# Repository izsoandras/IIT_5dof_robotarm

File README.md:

Foun an old 5 degree of freedom robotarm (Kalms&Mürb teach-robot) on my department. Decided to give it a new life. here is my progression.

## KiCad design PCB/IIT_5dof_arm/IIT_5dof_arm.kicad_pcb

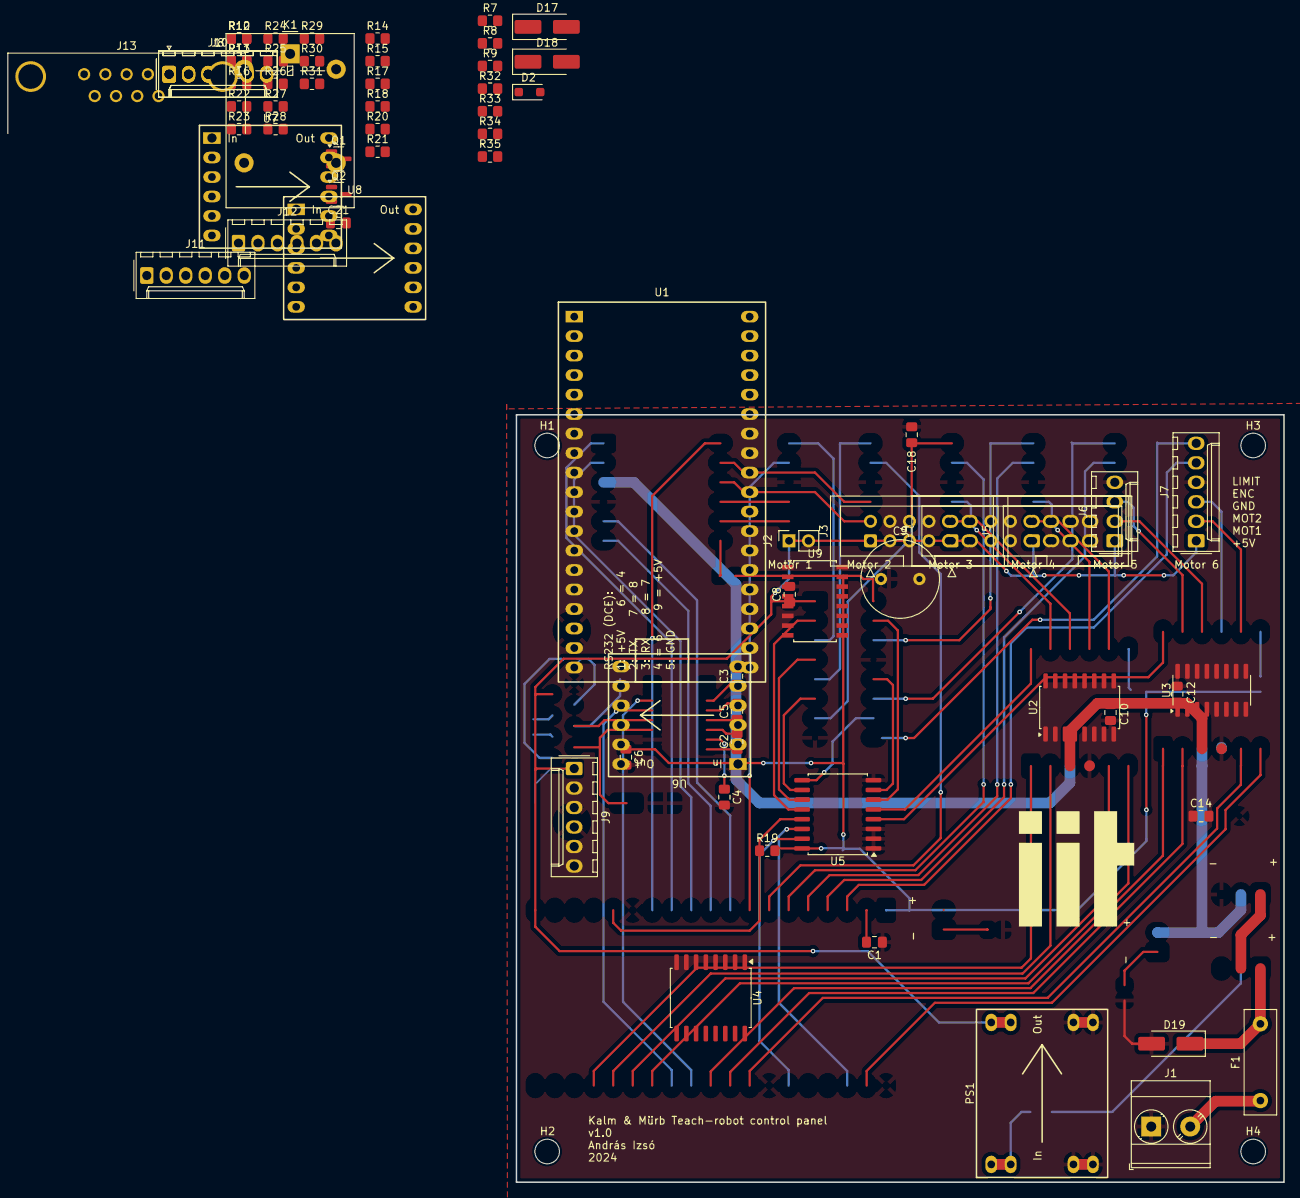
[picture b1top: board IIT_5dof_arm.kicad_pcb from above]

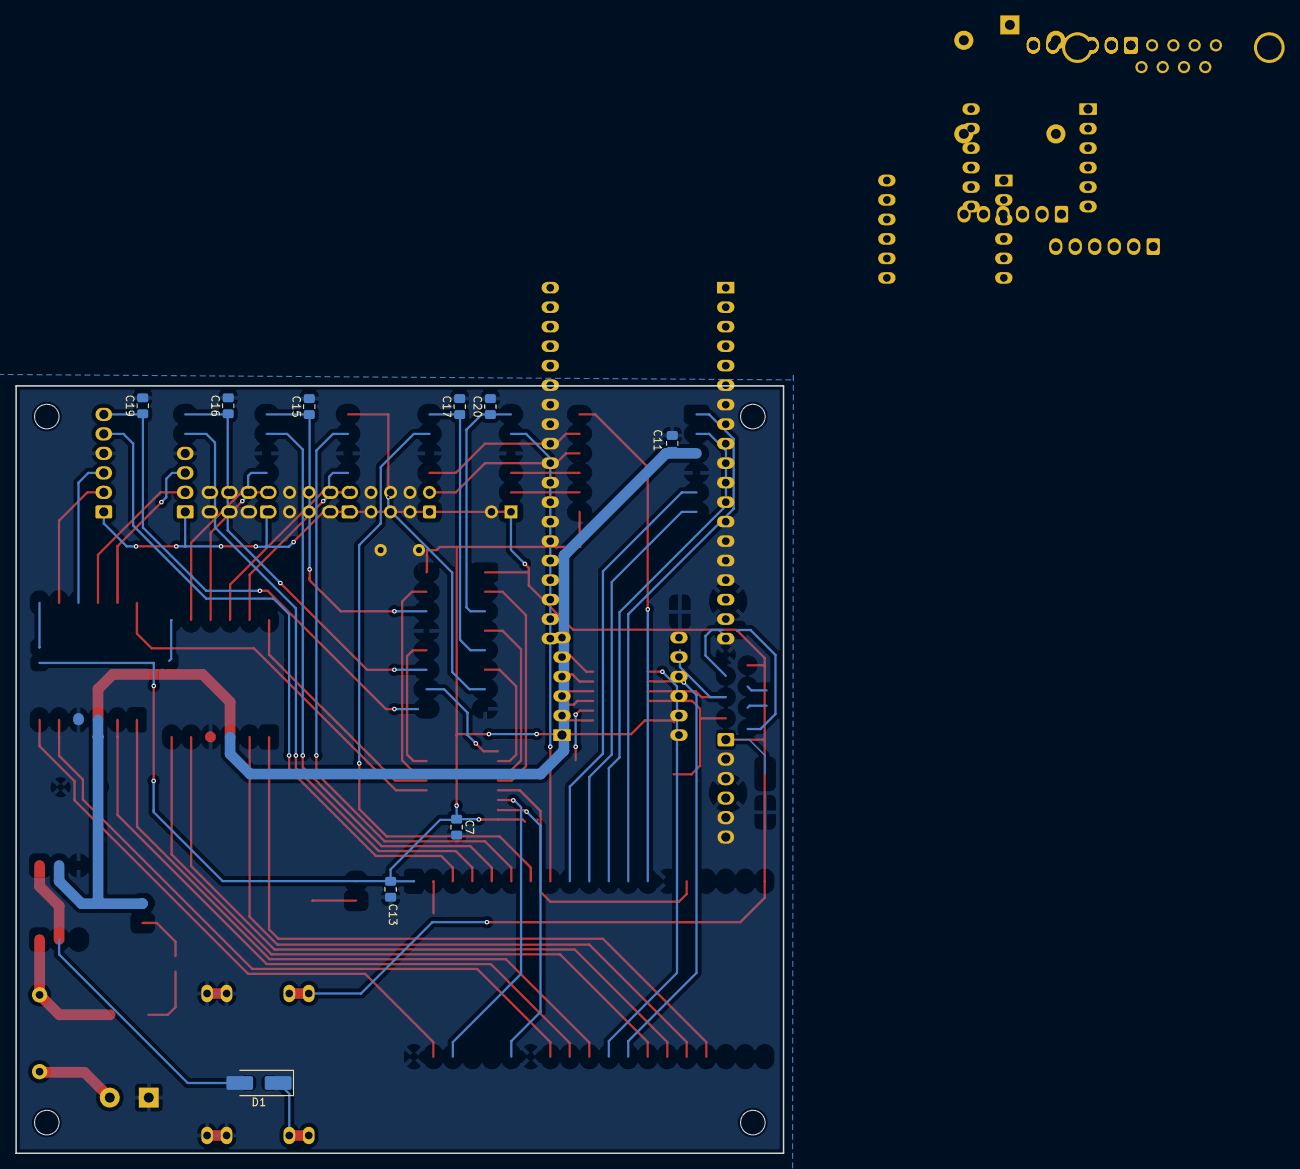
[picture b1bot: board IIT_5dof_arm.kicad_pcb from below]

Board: 2 copper layers, 100.0 x 100.0 mm, 86 parts (9 on the bottom side), 105 nets.

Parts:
C1, C10, C11, C13, C14, C17, C18, C19, C20, C21: 0.1uF; C_0805_2012Metric_Pad1.18x1.45mm_HandSolder
C2, C3, C4, C5, C6, C7, C8: 10nF; C_0805_2012Metric_Pad1.18x1.45mm_HandSolder
C9: 1000uF; C_Radial_D10.0mm_H16.0mm_P5.00mm
C12, C15, C16: 10uF; C_0805_2012Metric_Pad1.18x1.45mm_HandSolder
D1, D17, D18: SMAJ12A; D_SMA_Handsoldering
D2: D_Schottky; D_SOD-123F
D19: SMAJ5.0A; D_SMA_Handsoldering
F1: 30R500UF; C_Rect_L13.5mm_W4.0mm_P10.00mm_FKS3_FKP3_MKS4
H1, H2, H3, H4: MountingHole; MountingHole_3.2mm_M3
J1: Screw_Terminal_01x02; TerminalBlock_Phoenix_MKDS-3-2-5.08_1x02_P5.08mm_Horizontal
J2: Conn_01x02; PinSocket_1x02_P2.54mm_Vertical
J3: Conn_02x06_Odd_Even; IDC-Header_2x06_P2.54mm_Vertical
J4: Conn_02x08_Odd_Even; IDC-Header_2x08_P2.54mm_Vertical
J5: Conn_02x04_Odd_Even; IDC-Header_2x04_P2.54mm_Vertical
J6: Conn_01x04; Molex_KK-254_AE-6410-04A_1x04_P2.54mm_Vertical
J7, J8, J9, J10, J11, J12: Conn_01x06; Molex_KK-254_AE-6410-06A_1x06_P2.54mm_Vertical
J13: DE9_Receptacle_MountingHoles; DSUB-9_Female_Horizontal_P2.77x2.84mm_EdgePinOffset4.94mm_H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
K1: G5LE-1; Relay_SPDT_Omron-G5LE-1
PS1: DSN-1504
Q1, Q2: 2N7002; SOT-23
R7: 220; R_0805_2012Metric_Pad1.20x1.40mm_HandSolder
R8: 100k; R_0805_2012Metric_Pad1.20x1.40mm_HandSolder
R9, R13, R14, R16, R24, R25, R26, R27, R29, R31, R33: 10k; R_0805_2012Metric_Pad1.20x1.40mm_HandSolder
R10, R11, R12, R15, R17, R32, R34: 1k; R_0805_2012Metric_Pad1.20x1.40mm_HandSolder
R18, R19, R20, R21, R22, R23: 3k; R_0805_2012Metric_Pad1.20x1.40mm_HandSolder
R28, R30: 4k7; R_0805_2012Metric_Pad1.20x1.40mm_HandSolder
R35: 2k; R_0805_2012Metric_Pad1.20x1.40mm_HandSolder
U1: NodeMCU32S
U2: 74LS157; SO-16_5.3x10.2mm_P1.27mm
U3: 4504; SOIC-16_3.9x9.9mm_P1.27mm
U4, U5: XL8574T; SOIC-16W_7.5x10.3mm_P1.27mm
U6, U7, U8: DRV8833-M
U9: MAX3232; SOIC-16W_5.3x10.2mm_P1.27mm

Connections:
+3V3: C1.2, C11.1, C13.1, C14.1, C19.1, J3.1, J3.3, J3.5, J3.7, J3.9, J3.11, J4.5, J4.9, J4.13, J4.15, R24.2, R25.1, R26.1, R27.1, R28.2, R29.1, R30.2, R31.1, U1.1 (3v3), U2.16 (VCC), U3.16 (VDD), U4.16 (VDD), U5.16 (VDD), U9.16 (VCC)
+5V: C10.1, D19.1 (A1), J6.1, J7.1, J8.1, J9.1, J10.1, J11.1, J12.1, J13.1, J13.9, K1.5, PS1.4 (Vout), R33.1, U1.19 (Vin), U3.1 (VCC)
+15V: D1.1 (A1), F1.2, J5.1
/EMG_LED-: J4.10, R10.1
/EMG_signal: J5.5, Q1.1 (G), R10.2, R34.2, R35.1, U1.3 (GPIO36/ADC0)
/EMG_signal_5V: J13.7, R33.2, R34.1
/ESP-CAM/RX: J6.2, U2.6 (I1b)
/ESP-CAM/TX: J6.3, U2.9 (Zc)
/EspRST: C2.2, J2.1, U1.2 (RESET/EN)
/LED_3v3-: J4.6, R15.1
/LED_MotPower-: J4.8, R16.1
/LED_PowerOn-: J4.2, R13.1
/LED_VCC-: J4.4, R14.1
/Limit1_LED-: J3.2, R23.1
/Limit2_LED-: J3.4, R22.1
/Limit3_LED-: J3.6, R21.1
/Limit4_LED-: J3.8, R20.1
/Limit5_LED-: J3.10, R19.1
/Limit6_LED-: J3.12, R18.1
/Man/Aut SW: J5.7, R31.2, U4.5 (P1)
/Mot1_ENC: J7.5, U2.5 (I0b), U2.13 (I1d)
/Mot1_ENC/ESP-CAM_RX: U1.9 (GPIO25/ADC18/DAC1), U2.7 (Zb)
/Mot1_LIMIT: U3.2 (Aout), U5.12 (P7)
/Mot1_LIMIT_IN: C3.1, J7.6, U3.3 (Ain)
/Mot1_OUT1: J7.2, U7.8 (Out1_A)
/Mot1_OUT2: J7.3, U7.9 (Out1_B)
/Mot2_ENC: J8.5, U1.8 (GPIO33/ADC5/TOUCH8)
/Mot2_LIMIT: U3.4 (Bout), U5.11 (P6)
/Mot2_LIMIT_IN: C4.1, J8.6, U3.5 (Bin)
/Mot2_OUT1: J8.2, U7.10 (Out2_A)
/Mot2_OUT2: J8.3, U7.11 (Out2_B)
/Mot3_ENC: J9.5, U1.7 (GPIO32/ADC4/TOUCH9)
/Mot3_LIMIT: U3.6 (Cout), U5.10 (P5)
/Mot3_LIMIT_IN: C5.1, J9.6, U3.7 (Cin)
/Mot3_OUT1: J9.2, U6.10 (Out2_A)
/Mot3_OUT2: J9.3, U6.11 (Out2_B)
/Mot4_ENC: J10.5, U1.6 (GPIO35/ADC7)
/Mot4_LIMIT: U3.15 (Fout), U5.6 (P2)
/Mot4_LIMIT_IN: C6.1, J10.6, U3.14 (Fin)
/Mot4_OUT1: J10.2, U6.8 (Out1_A)
/Mot4_OUT2: J10.3, U6.9 (Out1_B)
/Mot5_ENC: J11.5, U1.5 (GPIO34/ADC6)
/Mot5_LIMIT: U3.12 (Eout), U5.7 (P3)
/Mot5_LIMIT_IN: C7.1, J11.6, U3.11 (Ein)
/Mot5_OUT1: J11.2, U8.10 (Out2_A)
/Mot5_OUT2: J11.3, U8.11 (Out2_B)
/Mot6_ENC: J12.5, U1.4 (GPIO39/ADC3)
/Mot6_LIMIT: U3.10 (Dout), U5.9 (P4)
/Mot6_LIMIT_IN: C8.1, J12.6, U3.9 (Din)
/Mot6_OUT1: J12.2, U8.8 (Out1_A)
/Mot6_OUT2: J12.3, U8.9 (Out1_B)
/MotEnable: R7.1, U4.6 (P2)
/MotPower: C12.1, C15.1, C16.1, J4.7, K1.1, U6.3 (VM), U7.3 (VM), U8.3 (VM)
/PowerOn: D2.2 (A), J4.1, J5.2, J5.3
/SCL_3v3: R28.1, U1.36 (GPIO22/I2C-SCL), U4.14 (SCL), U5.14 (SCL)
/SDA_3v3: R30.1, U1.33 (GPIO21/I2C-SDA), U4.15 (SDA), U5.15 (SDA)
/TBD_Led1: R11.2, U4.11 (P6)
/TBD_Led1-: J4.14, R11.1
/TBD_Led2: R12.2, U4.12 (P7)
/TBD_Led2-: J4.16, R12.1
/UI_RX_3v3: U1.27 (GPIO16/RX2), U9.12 (R1OUT)
/UI_RX_5v: D17.1 (A1), J13.3, U9.13 (R1IN)
/UI_TX_3v3: U1.28 (GPIO17/TX2), U9.11 (T1IN)
/UI_TX_5v: D18.1 (A1), J13.2, U9.14 (T1OUT)
/alt_mot1A: U2.3 (I1a), U4.9 (P4)
/alt_mot1_enc: U2.12 (Zd), U4.10 (P5)
/extender_INT: R24.1, U1.15 (GPIO13/ADC14/TOUCH4/SPI-MOSI), U4.13 (~INT), U5.13 (~INT)
/mot1_A: U2.4 (Za), U7.1 (IN1_A)
/mot1_A/ESP-CAM_TX: U1.13 (GPIO12/ADC15/TOUCH5/SPI-MISO), U2.2 (I0a), U2.10 (I1c)
/mot1_B: U1.12 (GPIO14/ADC16/TOUCH6/SPI-CLK), U7.2 (IN1_B)
/mot2_A: U1.10 (GPIO26/ADC19/DAC2), U7.5 (IN2_A)
/mot2_B: U1.11 (GPIO27/ADC17/TOUCH7), U7.6 (IN2_B)
/mot3_A: U1.25 (GPIO0/ADC11/TOUCH1), U6.5 (IN2_A)
/mot3_B: U1.26 (GPIO4/ADC10/TOUCH0), U6.6 (IN2_B)
/mot4_A: U1.23 (GPIO15/ADC13/TOUCH3), U6.1 (IN1_A)
/mot4_B: U1.24 (GPIO2/ADC12/TOUCH2), U6.2 (IN1_B)
/mot5_A: U1.29 (GPIO5/VSPI-SS), U8.1 (IN1_A)
/mot5_B: U1.30 (GPIO18/VSPI-SCK), U8.2 (IN1_B)
/mot6_A: U1.31 (GPIO19/VSPI-MISO), U8.5 (IN2_A)
/mot6_B: U1.37 (GPIO23/VSPI-MOSI), U8.6 (IN2_B)
/useESP-CAM: R17.1, U2.1 (S), U4.7 (P3)
/useESP-CAM_LED+: J4.11, R17.2
/~Fault_12: U4.4 (P0), U7.12 (~Fault)
/~Fault_34: U5.5 (P1), U6.12 (~Fault)
/~Fault_56: U5.4 (P0), U8.12 (~Fault)
/~Sleep_12: R26.2, U7.7 (~Sleep)
/~Sleep_34: R25.2, U6.7 (~Sleep)
/~Sleep_56: R27.2, U8.7 (~Sleep)
GND: C1.1, C2.1, C3.2, C4.2, C5.2, C6.2, C7.2, C8.2, C9.2, C10.2, C11.2, C12.2, C13.2, C14.2, C15.2, C16.2, C19.2, C20.2, C21.2, D1.2 (A2), D17.2 (A2), D18.2 (A2), D19.2 (A2), J1.1, J2.2, J4.12, J5.6, J5.8, J6.4, J7.4, J8.4, J9.4, J10.4, J11.4, J12.4, J13.0 (PAD), J13.5, PS1.2 (GNDin), PS1.3 (GNDout), Q2.2 (S), R8.2, R9.2, R13.2, R14.2, R15.2, R16.2, R18.2, R19.2, R20.2, R21.2, R22.2, R23.2, R35.2, U1.14 (GND), U1.32 (GND), U1.38 (GND), U2.8 (GND), U3.8 (VSS), U3.13 (Select), U4.2 (A1), U4.3 (A2), U4.8 (VSS), U5.1 (A0), U5.2 (A1), U5.3 (A2), U5.8 (VSS), U6.4 (GND), U7.4 (GND), U8.4 (GND), U9.15 (GND)
unnamed: D2.1 (K), PS1.1 (Vin)
unnamed: F1.1, J1.2
unnamed: J13.4, R32.1
unnamed: J13.6, R32.2
unnamed: K1.2, Q1.3 (D)
unnamed: Q1.2 (S), Q2.3 (D)
unnamed: Q2.1 (G), R7.2, R8.1
unnamed: R9.1, U2.11 (I0c), U2.14 (I0d), U2.15 (E)
unnamed: R29.2, U4.1 (A0)
unnamed: C17.1, U9.1 (C1+)
unnamed: C17.2, U9.3 (C1-)
unnamed: C18.1, U9.4 (C2+)
unnamed: C18.2, U9.5 (C2-)
unnamed: C21.1, U9.2 (VS+)
unnamed: C20.1, U9.6 (VS-)
VCC: C9.1, J4.3, J5.4, K1.3

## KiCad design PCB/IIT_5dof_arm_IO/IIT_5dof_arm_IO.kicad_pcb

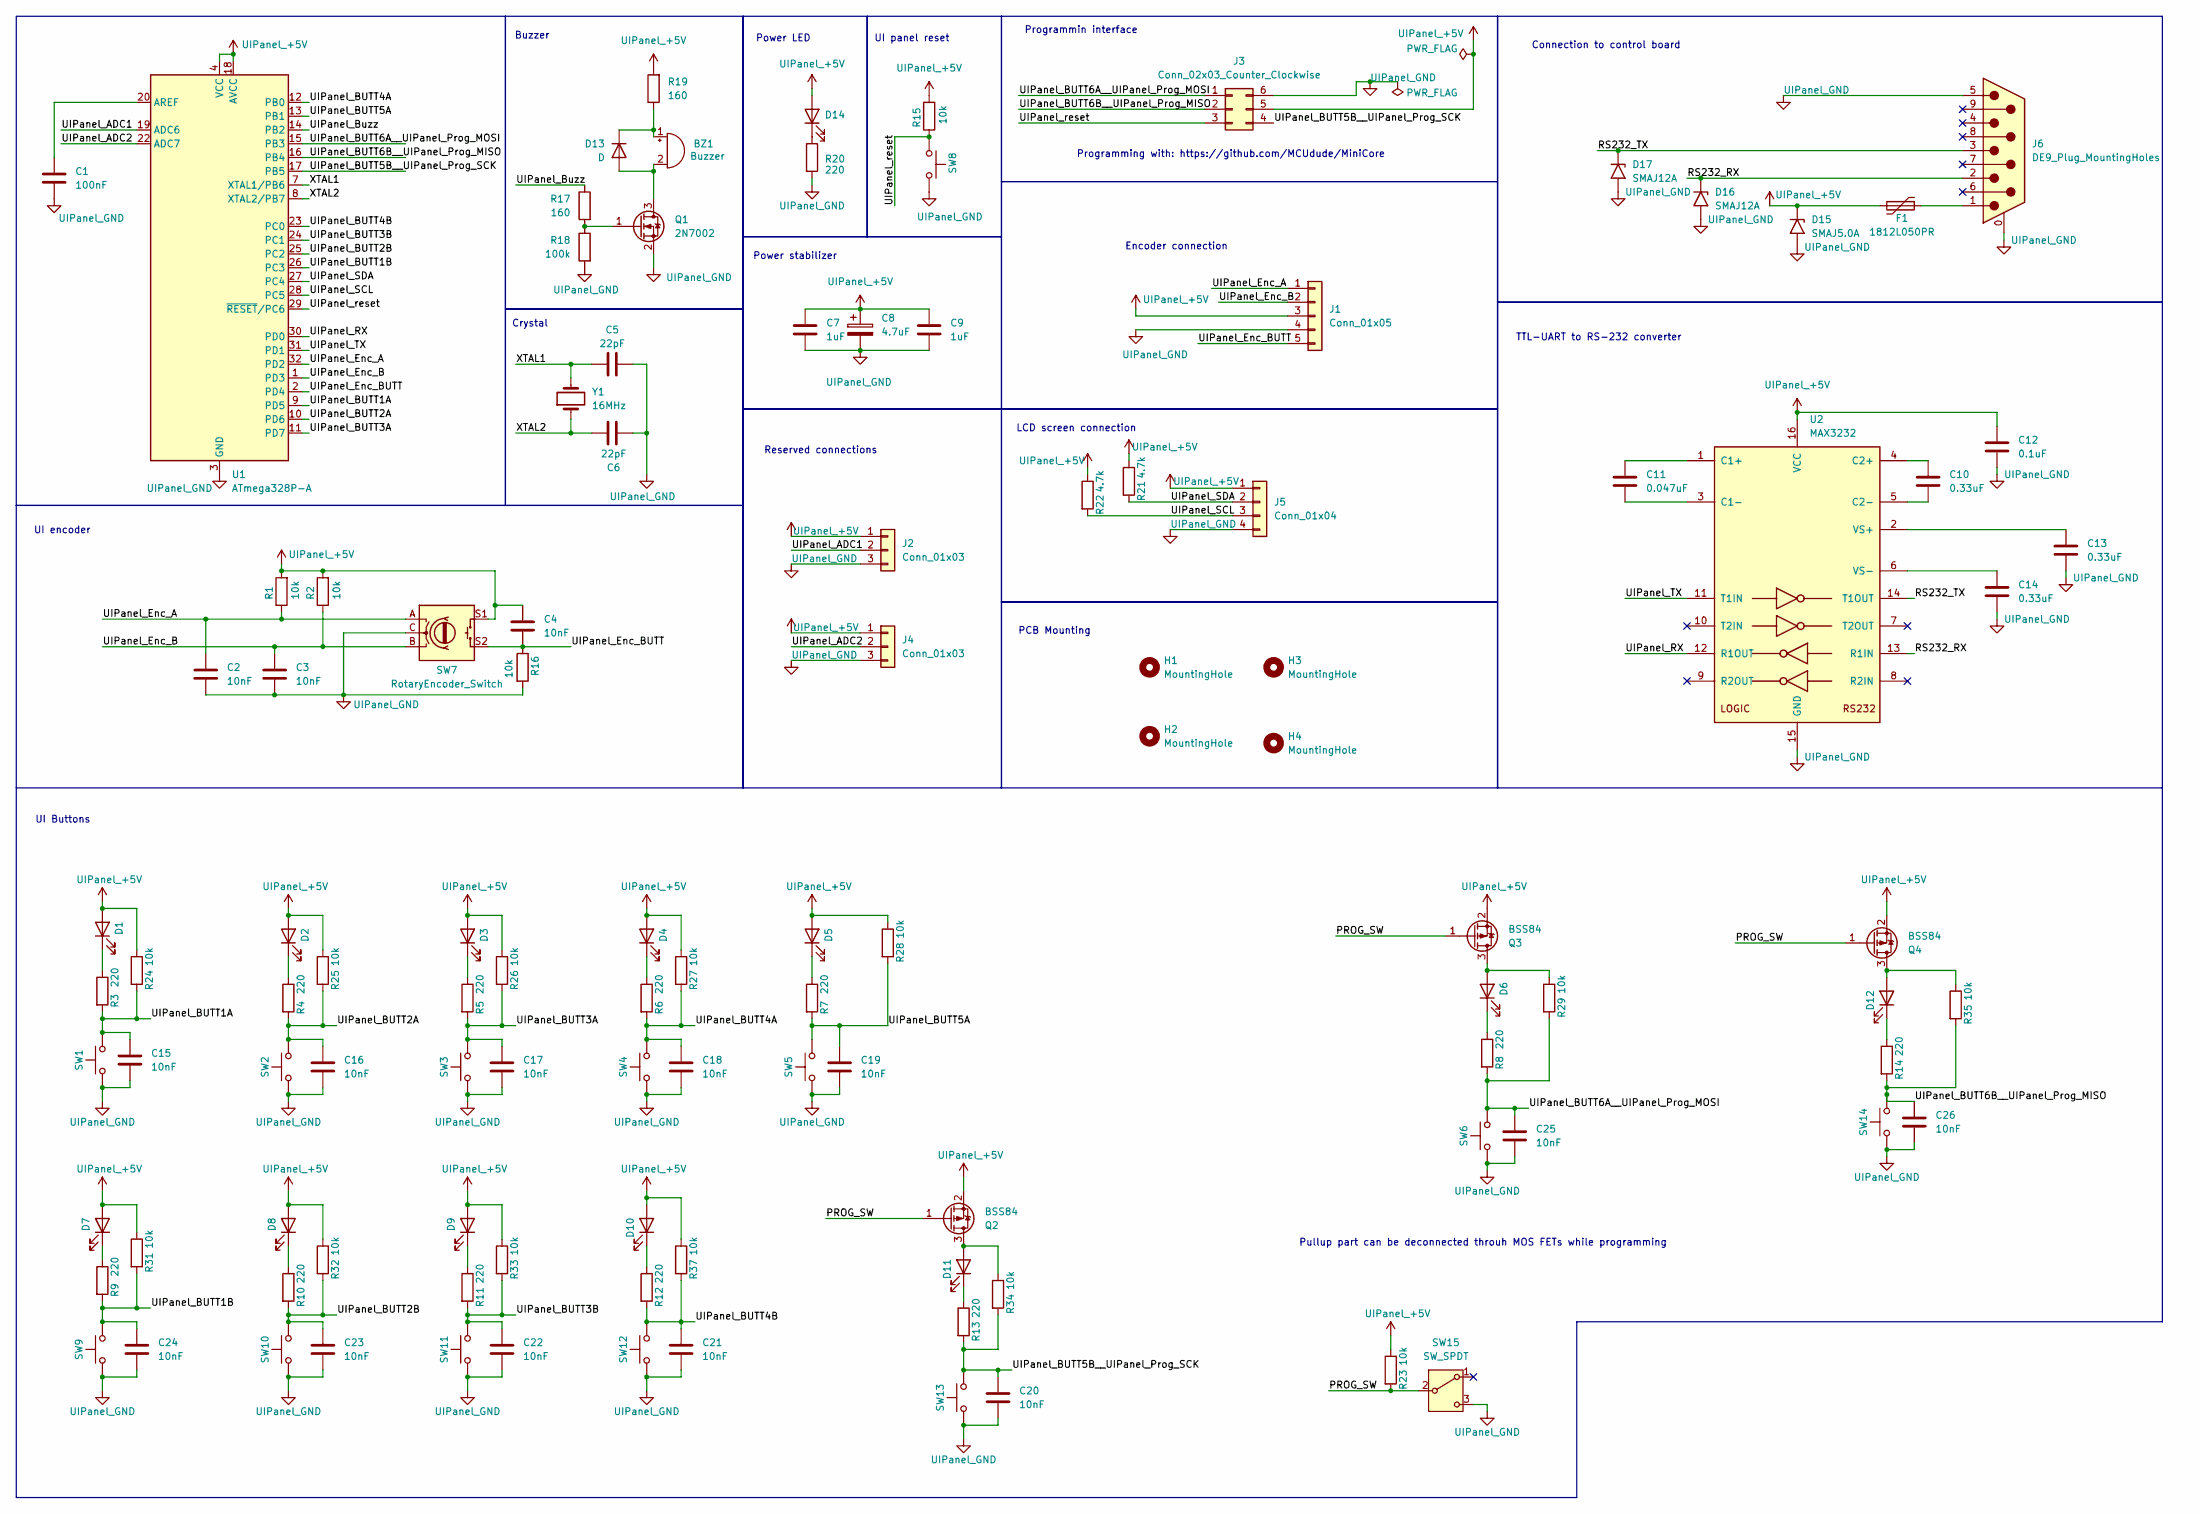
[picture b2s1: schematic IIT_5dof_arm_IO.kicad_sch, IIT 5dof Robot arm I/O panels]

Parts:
BZ1: Buzzer; Molex_KK-254_AE-6410-02A_1x02_P2.54mm_Vertical
C1: 100nF; C_0805_2012Metric_Pad1.18x1.45mm_HandSolder
C2, C3, C4, C15, C16, C17, C18, C19, C20, C21, C22, C23, C24, C25, C26: 10nF; C_0805_2012Metric_Pad1.18x1.45mm_HandSolder
C5, C6: 22pF; C_0805_2012Metric_Pad1.18x1.45mm_HandSolder
C7, C9: 1uF; C_0805_2012Metric_Pad1.18x1.45mm_HandSolder
C8: 4.7uF; C_1206_3216Metric_Pad1.33x1.80mm_HandSolder
C10, C13, C14: 0.33uF; C_0805_2012Metric_Pad1.18x1.45mm_HandSolder
C11: 0.047uF; C_0805_2012Metric_Pad1.18x1.45mm_HandSolder
C12: 0.1uF; C_0805_2012Metric_Pad1.18x1.45mm_HandSolder
D1, D2, D3, D4, D5, D6, D7, D8, D9, D10, D11, D12, D14: LED; Molex_KK-254_AE-6410-02A_1x02_P2.54mm_Vertical
D13: D; D_0805_2012Metric_Pad1.15x1.40mm_HandSolder
D15: SMAJ5.0A; D_SMA
D16, D17: SMAJ12A; D_SMA
F1: 1812L050PR; 1812L050PR__1.78mm_3.15mm_3.45mm
H1, H2, H3, H4: MountingHole; MountingHole_3.2mm_M3
J1: Conn_01x05; Molex_KK-254_AE-6410-05A_1x05_P2.54mm_Vertical
J2, J4: Conn_01x03; Molex_KK-254_AE-6410-03A_1x03_P2.54mm_Vertical
J3: Conn_02x03_Counter_Clockwise; PinHeader_2x03_P2.54mm_Vertical
J5: Conn_01x04; Molex_KK-254_AE-6410-04A_1x04_P2.54mm_Vertical
J6: DE9_Plug_MountingHoles; DSUB-9_Male_Horizontal_P2.77x2.84mm_EdgePinOffset7.70mm_Hou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
Q1: 2N7002; SOT-23
Q2, Q3, Q4: BSS84; SOT-23
R1, R2, R15, R16, R23, R24, R25, R26, R27, R28, R29, R31, R32, R33, R34, R35, R37: 10k; R_0805_2012Metric_Pad1.20x1.40mm_HandSolder
R3, R4, R5, R6, R7, R8, R9, R10, R11, R12, R13, R14, R20: 220; R_0805_2012Metric_Pad1.20x1.40mm_HandSolder
R17, R19: 160; R_0805_2012Metric_Pad1.20x1.40mm_HandSolder
R18: 100k; R_0805_2012Metric_Pad1.20x1.40mm_HandSolder
R21, R22: 4.7k; R_0805_2012Metric_Pad1.20x1.40mm_HandSolder
SW1, SW2, SW3, SW4, SW5, SW6, SW9, SW10, SW11, SW12, SW13, SW14: SW_Push; Molex_KK-254_AE-6410-02A_1x02_P2.54mm_Vertical
SW7: RotaryEncoder_Switch; Molex_for_encoder_1x05_P2.54mm_Vertical
SW8: SW_Push; SW_SPST_FSMSM
SW15: SW_SPDT; PinHeader_1x03_P2.54mm_Vertical
U1: ATmega328P-A; TQFP-32_7x7mm_P0.8mm
U2: MAX3232; SOIC-16W_5.3x10.2mm_P1.27mm
Y1: 16MHz; Crystal_SMD_HC49-SD_HandSoldering

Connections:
/PROG_SW: Q2.1 (G), Q3.1 (G), Q4.1 (G), R23.2, SW15.2 (B)
/RS232_RX: D16.1 (A1), J6.2, U2.13 (R1IN)
/RS232_TX: D17.1 (A1), J6.3, U2.14 (T1OUT)
/UIPanel_ADC1: J2.2, U1.19 (ADC6)
/UIPanel_ADC2: J4.2, U1.22 (ADC7)
/UIPanel_BUTT1A: C15.1, R3.2, R24.2, SW1.2, U1.9 (PD5)
/UIPanel_BUTT1B: C24.1, R9.2, R31.2, SW9.1, U1.26 (PC3)
/UIPanel_BUTT2A: C16.1, R4.2, R25.2, SW2.2, U1.10 (PD6)
/UIPanel_BUTT2B: C23.1, R10.2, R32.2, SW10.1, U1.25 (PC2)
/UIPanel_BUTT3A: C17.1, R5.2, R26.2, SW3.2, U1.11 (PD7)
/UIPanel_BUTT3B: C22.1, R11.2, R33.2, SW11.1, U1.24 (PC1)
/UIPanel_BUTT4A: C18.1, R6.2, R27.2, SW4.2, U1.12 (PB0)
/UIPanel_BUTT4B: C21.1, R12.2, R37.2, SW12.1, U1.23 (PC0)
/UIPanel_BUTT5A: C19.1, R7.2, R28.2, SW5.2, U1.13 (PB1)
/UIPanel_BUTT5B__UIPanel_Prog_SCK: C20.1, J3.4, R13.2, R34.2, SW13.1, U1.17 (PB5)
/UIPanel_BUTT6A__UIPanel_Prog_MOSI: C25.1, J3.1, R8.2, R29.2, SW6.2, U1.15 (PB3)
/UIPanel_BUTT6B__UIPanel_Prog_MISO: C26.1, J3.2, R14.2, R35.2, SW14.1, U1.16 (PB4)
/UIPanel_Buzz: R17.1, U1.14 (PB2)
/UIPanel_Enc_A: C2.1, J1.1, R1.1, SW7.A, U1.32 (PD2)
/UIPanel_Enc_B: C3.1, J1.2, R2.1, SW7.B, U1.1 (PD3)
/UIPanel_Enc_BUTT: C4.2, J1.5, R16.1, SW7.S2, U1.2 (PD4)
/UIPanel_RX: U1.30 (PD0), U2.12 (R1OUT)
/UIPanel_SCL: J5.3, R22.2, U1.28 (PC5)
/UIPanel_SDA: J5.2, R21.2, U1.27 (PC4)
/UIPanel_TX: U1.31 (PD1), U2.11 (T1IN)
/UIPanel_reset: J3.3, R15.1, SW8.1, U1.29 (~RESET/PC6)
/XTAL1: C5.1, U1.7 (XTAL1/PB6), Y1.2
/XTAL2: C6.2, U1.8 (XTAL2/PB7), Y1.1
unnamed: BZ1.1 (+), D13.1 (K), R19.1
unnamed: BZ1.2 (-), D13.2 (A), Q1.3 (D)
unnamed: D1.1 (K), R3.1
unnamed: D2.1 (K), R4.1
unnamed: D3.1 (K), R5.1
unnamed: D4.1 (K), R6.1
unnamed: D5.1 (K), R7.1
unnamed: D6.2 (A), Q3.3 (D), R29.1
unnamed: D6.1 (K), R8.1
unnamed: D7.1 (K), R9.1
unnamed: D8.1 (K), R10.1
unnamed: D9.1 (K), R11.1
unnamed: D10.1 (K), R12.1
unnamed: D11.2 (A), Q2.3 (D), R34.1
unnamed: D11.1 (K), R13.1
unnamed: D12.2 (A), Q4.3 (D), R35.1
unnamed: D12.1 (K), R14.1
unnamed: D14.1 (K), R20.1
unnamed: F1.1, J6.1
unnamed: Q1.1 (G), R17.2, R18.1
unnamed: C1.1, U1.20 (AREF)
unnamed: C11.1, U2.1 (C1+)
unnamed: C11.2, U2.3 (C1-)
unnamed: C10.1, U2.4 (C2+)
unnamed: C10.2, U2.5 (C2-)
unnamed: C13.1, U2.2 (VS+)
unnamed: C14.1, U2.6 (VS-)
UIPanel_+5V: C4.1, C7.1, C8.1, C9.1, C12.1, D1.2 (A), D2.2 (A), D3.2 (A), D4.2 (A), D5.2 (A), D7.2 (A), D8.2 (A), D9.2 (A), D10.2 (A), D14.2 (A), D15.1 (A1), F1.2, J1.3, J2.1, J3.5, J4.1, J5.1, Q2.2 (S), Q3.2 (S), Q4.2 (S), R1.2, R2.2, R15.2, R19.2, R21.1, R22.1, R23.1, R24.1, R25.1, R26.1, R27.1, R28.1, R31.1, R32.1, R33.1, R37.1, SW7.S1, U1.4 (VCC), U1.6 (VCC), U1.18 (AVCC), U2.16 (VCC)
UIPanel_GND: C1.2, C2.2, C3.2, C5.2, C6.1, C7.2, C8.2, C9.2, C12.2, C13.2, C14.2, C15.2, C16.2, C17.2, C18.2, C19.2, C20.2, C21.2, C22.2, C23.2, C24.2, C25.2, C26.2, D15.2 (A2), D16.2 (A2), D17.2 (A2), J1.4, J2.3, J3.6, J4.3, J5.4, J6.0 (PAD), J6.5, Q1.2 (S), R16.2, R18.2, R20.2, SW1.1, SW2.1, SW3.1, SW4.1, SW5.1, SW6.1, SW7.C, SW8.2, SW9.2, SW10.2, SW11.2, SW12.2, SW13.2, SW14.2, SW15.3 (C), U1.3 (GND), U1.5 (GND), U1.21 (GND), U2.15 (GND)

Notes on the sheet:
Crystal
Power LED
Connection to control board
Reserved connections
Programming with: https://github.com/MCUdude/MiniCore
Programmin interface
UI encoder
UI panel reset
PCB Mounting
Buzzer
UI Buttons
Encoder connection
LCD screen connection
Power stabilizer
Pullup part can be deconnected throuh MOS FETs while programming
TTL-UART to RS-232 converter

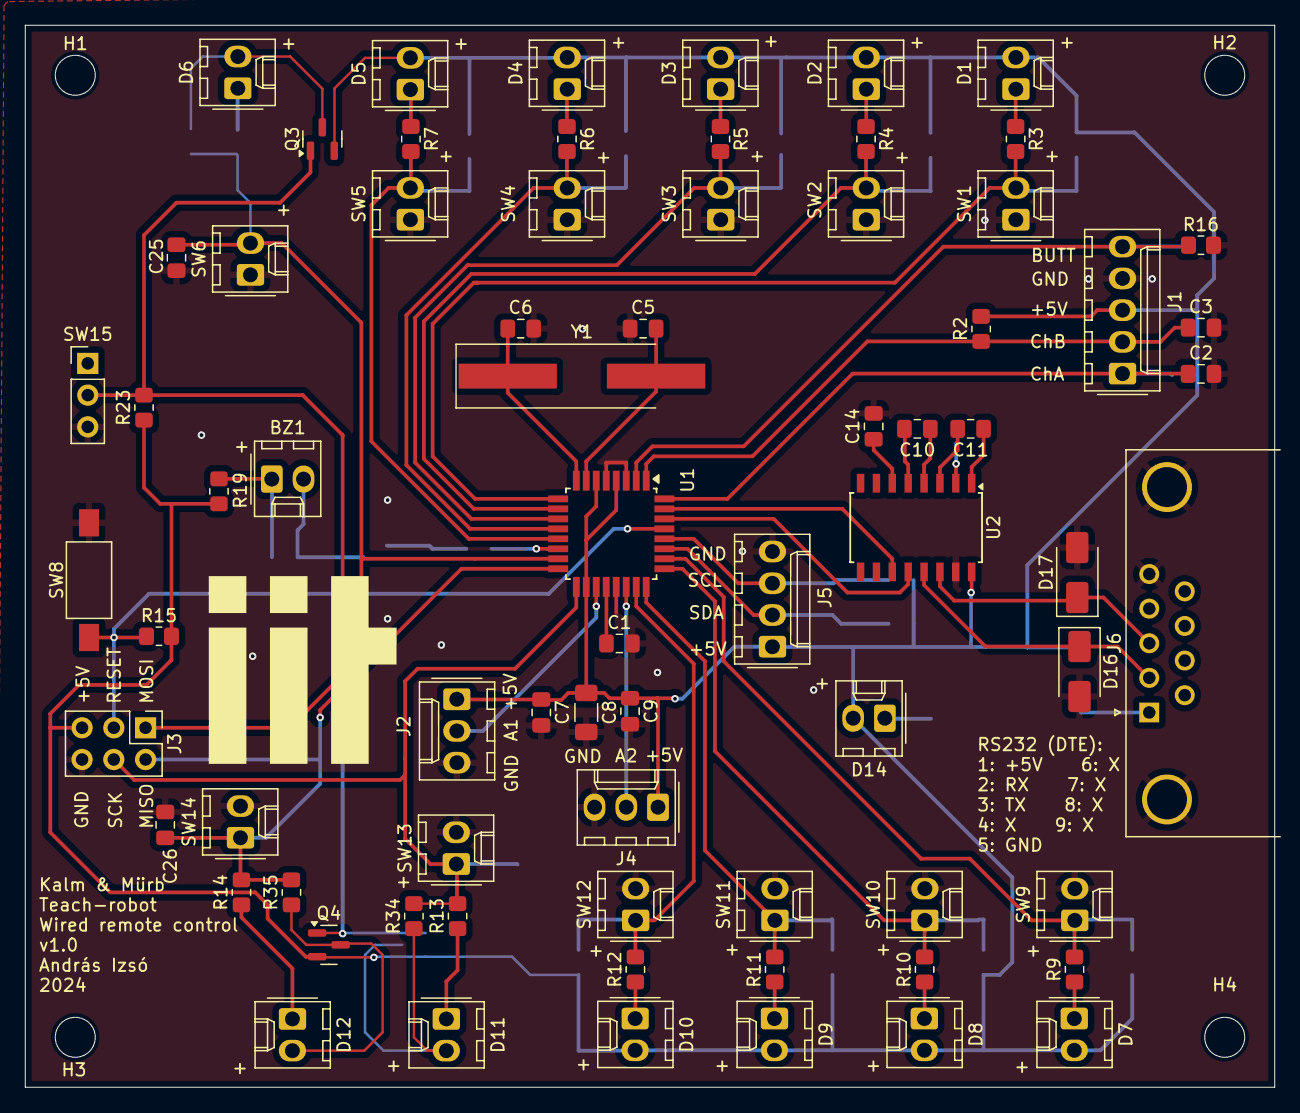
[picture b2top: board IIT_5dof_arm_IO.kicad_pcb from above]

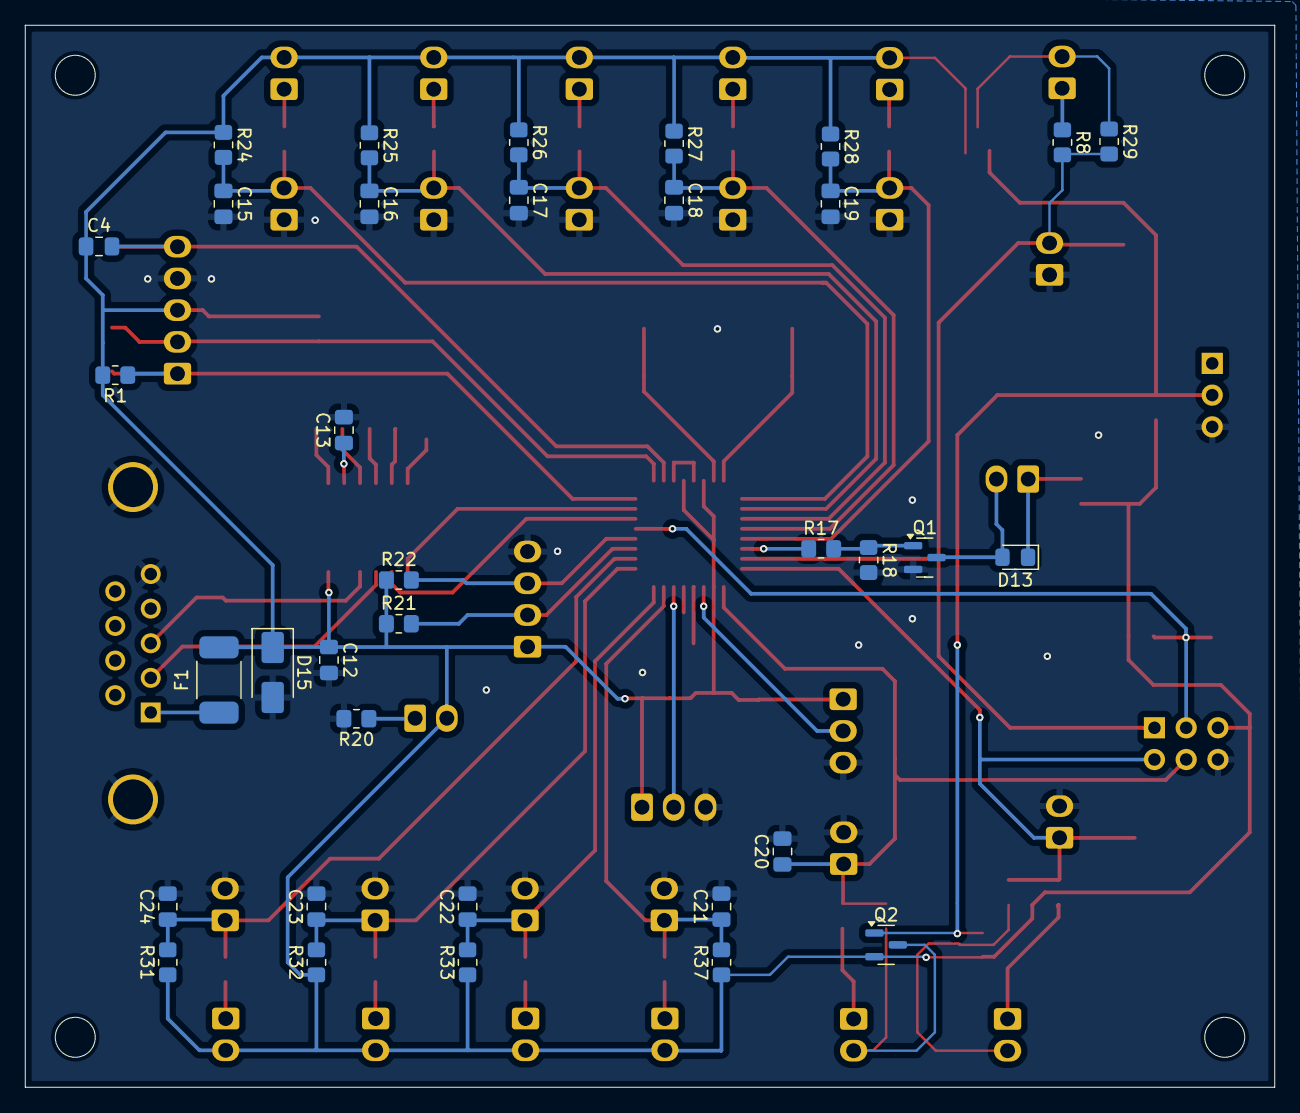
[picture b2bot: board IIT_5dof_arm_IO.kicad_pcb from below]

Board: 2 copper layers, 100.0 x 85.0 mm, 111 parts (35 on the bottom side), 57 nets.

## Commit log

2024-03-02 init, fixed LEDs, added I/O panels
2024-03-02 Update pdf export
2024-03-03 Separated UI to ATmega controller
2024-03-03 Switch UART level shift to 2in1 fet, resistor values corrected
2024-03-13 create separate project for IO board
2024-03-18 Fixed level shifting, power input protection, buzzer drive and UI buttons
2024-03-19 Added limit switches to schematic
2024-03-23 Split control board and I/O cards into separate projects
2024-03-23 Control board layout
2024-03-23 Change motor power LED footprint to connector
2024-03-23 Organize schematic and generate initi PCB
2024-03-25 implement RS232
2024-03-26 Extend ESD protection on RS-232 interface and tidy up schematic
2024-03-26 Update schematic pdf
2024-03-26 Add RS-232 interface
2024-03-27 Improve LED button pullups + add detach MOSFETs
2024-03-27 Add pdf print of schematic for easier examination
2024-03-27 Add fuse, footprint assignment, minor tidy up
2024-03-27 Enhance explanation of control panel RS-232 connections
2024-04-08 Revise footprints
2024-04-08 Add decoupling capacitors
2024-04-08 Correct typo in RS232 silkscreen
2024-04-08 PCB layout
2024-04-08 Decoupling capacitors layout
2024-04-08 Add layout prints
2024-04-08 Update schematic print
2024-09-21 Fix SMAJ value, program pullup switch
2024-09-21 Eliminate GNDPWR
2024-09-21 Fix schematic pdf export
2024-10-03 Remove unnecessary vias
2024-10-30 Update schematic with new functionalities
2024-11-02 Add potmeter, mot toggle to IO
2024-11-02 Add gitignore
2024-11-02 Organize schematic
